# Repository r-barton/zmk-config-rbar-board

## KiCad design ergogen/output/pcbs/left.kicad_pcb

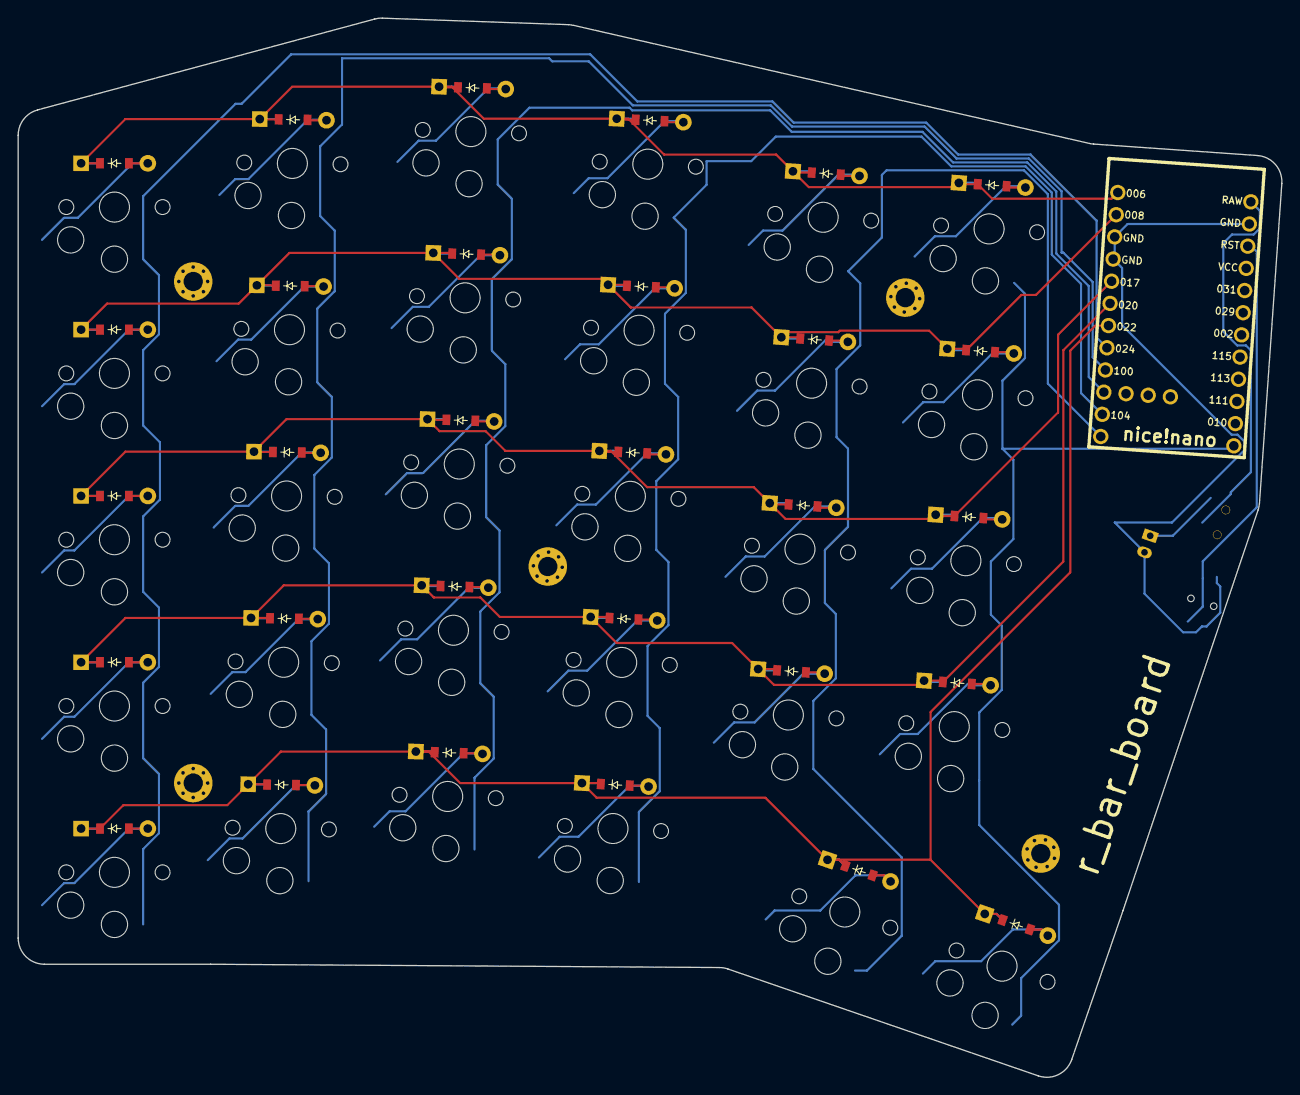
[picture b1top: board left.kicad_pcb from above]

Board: 2 copper layers, 144.4 x 121.0 mm, 69 parts (0 on the bottom side), 45 nets.

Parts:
B1: Panasonic_EVQPUL_EVQPUC
D1, D2, D3, D4, D5, D6, D7, D8, D9, D10, D11, D12, D13, D14, D15, D16, D17, D18, D19, D20, D21, D22, D23, D24, D25, D26, D27, D28, D29, D30: ComboDiode
JST1: JST_PH_S2B-PH-K_02x2.00mm_Angled
MCU1: nice_nano
S1, S2, S3, S4, S5, S6, S7, S8, S9, S10, S11, S12, S13, S14, S15, S16, S17, S18, S19, S20, S21, S22, S23, S24, S25, S26, S27, S28, S29, S30: PG1350
T1: SPDT_C128955
_1, _2, _3, _4, _5: MountingHole_2.2mm_M2_Pad_Via

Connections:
GND: B1.1, JST1.2, MCU1.3, MCU1.4, MCU1.23
P006: D5.1, D10.1, D15.1, D20.1, D24.1, D28.1, MCU1.1
P008: D4.1, D9.1, D14.1, D19.1, D23.1, D27.1, MCU1.2
P009: MCU1.13, S25.1, S26.1, S27.1, S28.1, S30.1
P011: MCU1.10, S11.1, S12.1, S13.1, S14.1, S15.1
P017: D3.1, D8.1, D13.1, D18.1, D22.1, D26.1, MCU1.5
P020: D2.1, D7.1, D12.1, D17.1, D21.1, D25.1, MCU1.6
P022: D1.1, D6.1, D11.1, D16.1, D29.1, D30.1, MCU1.7
P024: MCU1.8, S1.1, S2.1, S3.1, S4.1, S5.1
P100: MCU1.9, S6.1, S7.1, S8.1, S9.1, S10.1
P104: MCU1.11, S16.1, S17.1, S18.1, S19.1, S20.1
P106: MCU1.12, S21.1, S22.1, S23.1, S24.1, S29.1
RAW: MCU1.24, T1.2
RST: B1.2, MCU1.22
index_bottom: D21.2, S21.2
index_home: D22.2, S22.2
index_num: D24.2, S24.2
index_top: D23.2, S23.2
inner_bottom: D25.2, S25.2
inner_home: D26.2, S26.2
inner_num: D28.2, S28.2
inner_top: D27.2, S27.2
middle_bottom: D17.2, S17.2
middle_home: D18.2, S18.2
middle_mod: D16.2, S16.2
middle_num: D20.2, S20.2
middle_top: D19.2, S19.2
mod_thumb: D30.2, S30.2
outer_bottom: D2.2, S2.2
outer_home: D3.2, S3.2
outer_mod: D1.2, S1.2
outer_num: D5.2, S5.2
outer_top: D4.2, S4.2
pinky_bottom: D7.2, S7.2
pinky_home: D8.2, S8.2
pinky_mod: D6.2, S6.2
pinky_num: D10.2, S10.2
pinky_top: D9.2, S9.2
pos: JST1.1, T1.1
ring_bottom: D12.2, S12.2
ring_home: D13.2, S13.2
ring_mod: D11.2, S11.2
ring_num: D15.2, S15.2
ring_top: D14.2, S14.2
space_thumb: D29.2, S29.2

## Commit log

2024-08-24 Initial User Config.
2024-08-24 updating a bunch of files
2024-08-24 adding a gitignore
2024-08-24 Update keymap
2024-08-24 Move GH workflow back to root
2024-08-24 add ZEPHYR_BASE env variable
2024-08-24 Revert "add ZEPHYR_BASE env variable"
    This reverts commit 985188b3c5998eae8c355fbac612eb6df9dc4fb4.
2024-08-24 remove zephyr directory
2024-08-24 reorganize root directory
2024-08-24 rename with underscores
2024-08-24 Revert "remove zephyr directory"
    This reverts commit 191585c6b7205932c50b845e4c7f5a5a6a8c3875.
2024-08-24 move zephyr module.yml
2024-08-24 moving keymaps under a keyboard directory
2024-08-24 Ignore .zip files
2024-10-09 Update build.yaml
    Add a reset firmware
2024-10-09 Add experimental ble connection
2024-10-11 Re-doing the mounting holes because they were too small for M2 threaded inserts
2024-10-11 Update r_bar_board.keymap
    Add additional bluetooth profiles
2024-10-11 Update r_bar_board_left.conf
    Turn on deep sleep
2024-10-11 Update r_bar_board_right.conf
    turn on deep sleep
2024-10-11 Update r_bar_board.keymap
    Add output for preferring BLE over usb
2024-10-30 Update r_bar_board.keymap
    Add previous and next media controls
2025-07-06 add bluetooth toggle and usb binds
